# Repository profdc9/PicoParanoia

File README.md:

# PicoParanoia

This is an update to the ParanoiaBox ( https://www.github.com/profdc9/ParanoiaBox ) which uses a Raspberry Pi Pico rather than a STM32F103CBT6 Blue Pill.  It improves some security aspects of the original, such as having separate SPI ports for the ciphertext and plaintext cards.

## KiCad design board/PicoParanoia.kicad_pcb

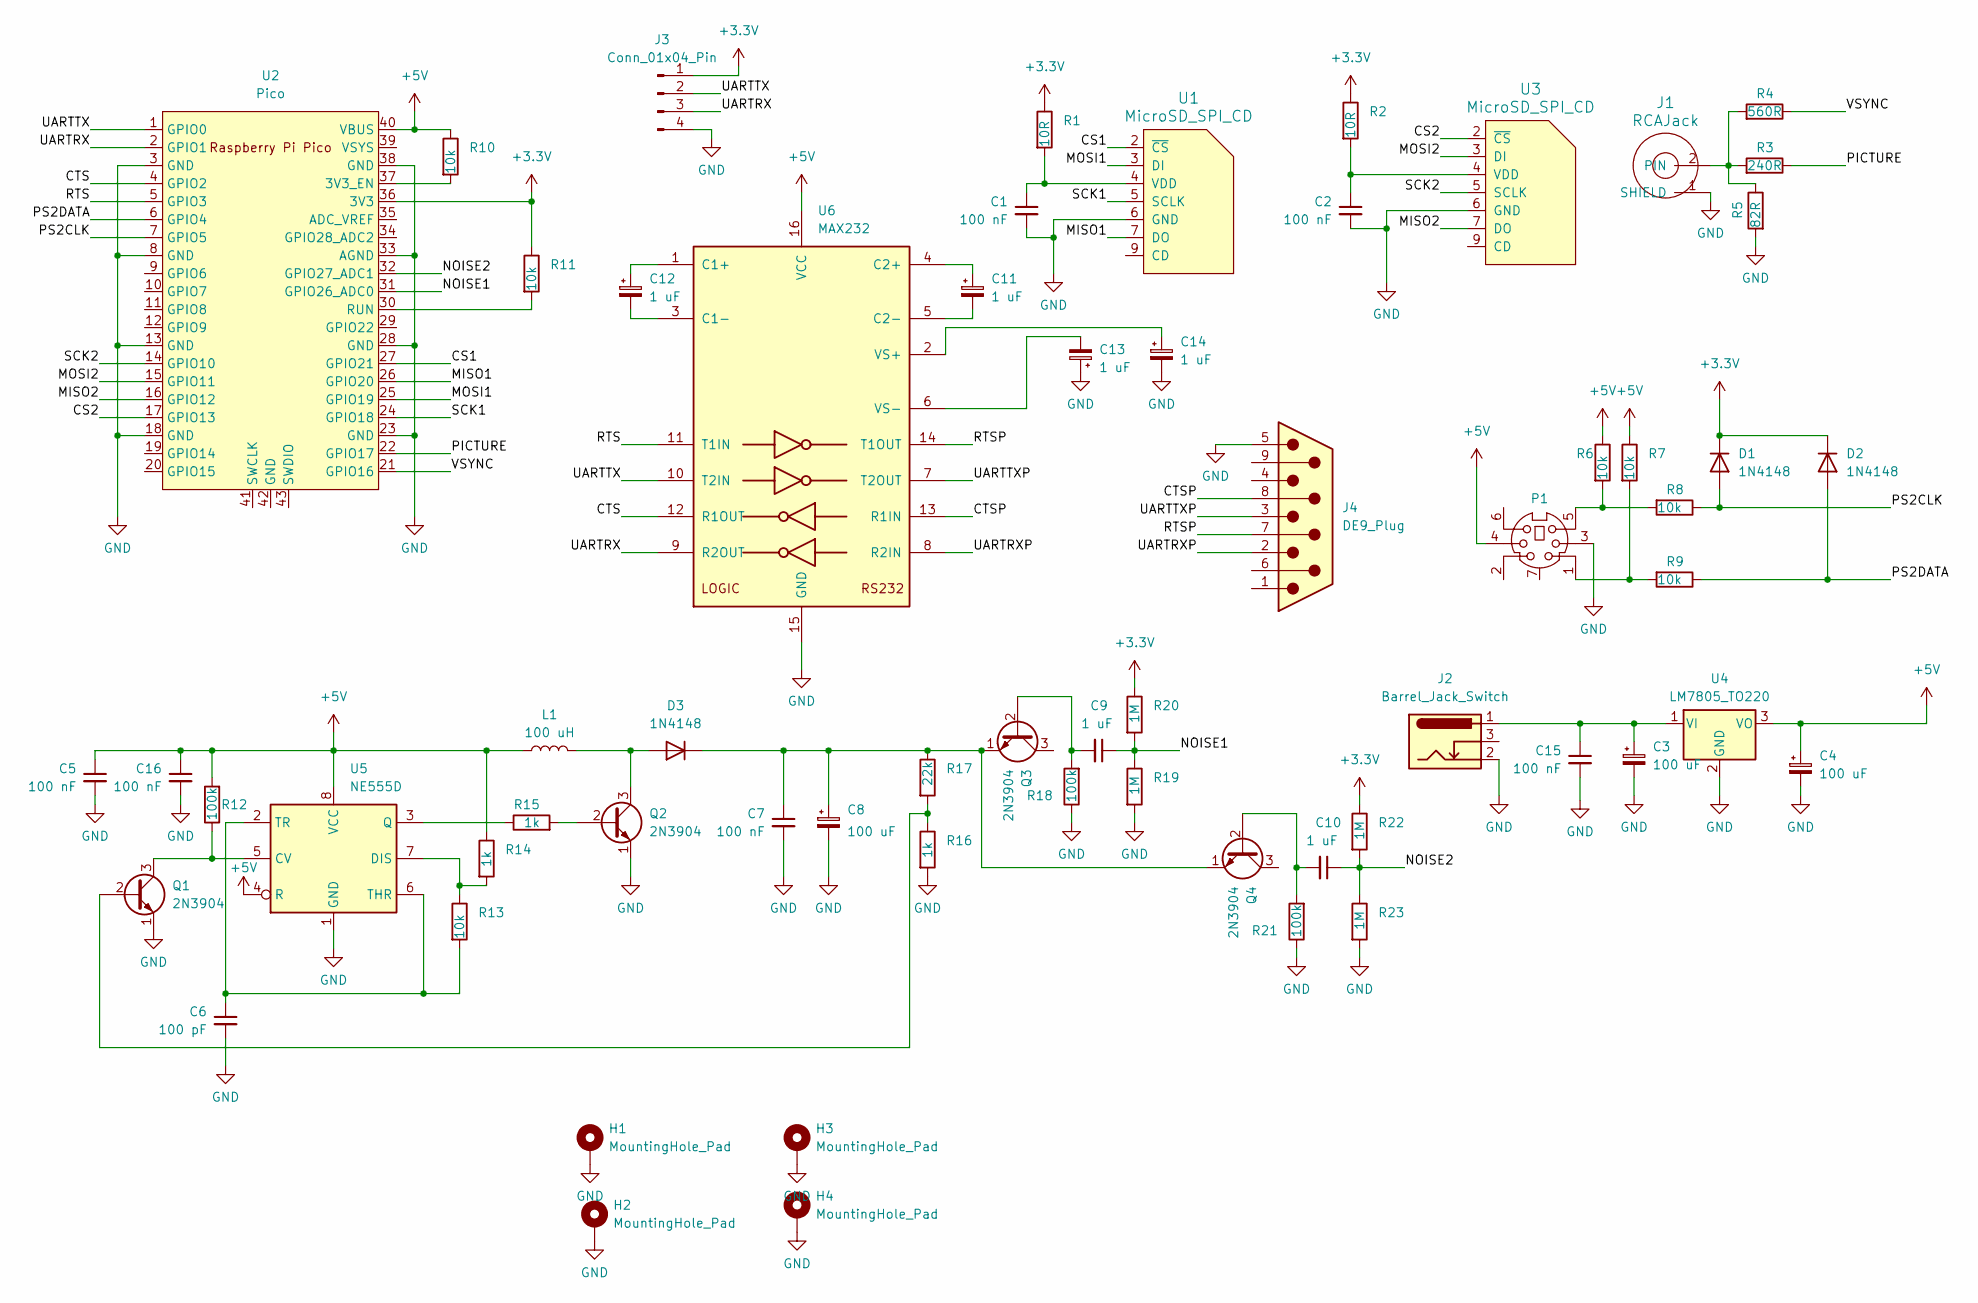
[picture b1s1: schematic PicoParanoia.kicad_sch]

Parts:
C1, C2, C5, C7, C15, C16: 100 nF; C_Disc_D5.0mm_W2.5mm_P5.00mm
C3, C4, C8: 100 uF; CP_Radial_D5.0mm_P2.50mm
C6: 100 pF; C_Disc_D5.0mm_W2.5mm_P5.00mm
C9, C10: 1 uF; C_Disc_D5.0mm_W2.5mm_P5.00mm
C11, C12, C13, C14: 1 uF; CP_Radial_D5.0mm_P2.50mm
D1, D2, D3: 1N4148; D_DO-41_SOD81_P7.62mm_Horizontal
H1, H2, H3, H4: MountingHole_Pad; MountingHole_3.2mm_M3_Pad
J1: RCAJack; RCAConnectorCommon
J2: Barrel_Jack_Switch; BarrelJack_Horizontal
J3: Conn_01x04_Pin; PinSocket_1x04_P2.54mm_Vertical
J4: DE9_Plug; DSUB-9_Male_Horizontal_P2.77x2.84mm_EdgePinOffset4.94mm_Hou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
L1: 100 uH; L_Axial_L7.0mm_D3.3mm_P12.70mm_Horizontal_Fastron_MICC
P1: Mini-DIN_6pins_ver4; Connector_Mini-DIN_Female_6Pin_2rows
Q1, Q2, Q3, Q4: 2N3904; TO-92_Inline_Wide
R1, R2: 10R; R_Axial_DIN0207_L6.3mm_D2.5mm_P7.62mm_Horizontal
R3: 240R; R_Axial_DIN0207_L6.3mm_D2.5mm_P7.62mm_Horizontal
R4: 560R; R_Axial_DIN0207_L6.3mm_D2.5mm_P7.62mm_Horizontal
R5: 82R; R_Axial_DIN0207_L6.3mm_D2.5mm_P7.62mm_Horizontal
R6, R7, R8, R9, R10, R11, R13: 10k; R_Axial_DIN0207_L6.3mm_D2.5mm_P7.62mm_Horizontal
R12, R18, R21: 100k; R_Axial_DIN0207_L6.3mm_D2.5mm_P7.62mm_Horizontal
R14, R15, R16: 1k; R_Axial_DIN0207_L6.3mm_D2.5mm_P7.62mm_Horizontal
R17: 22k; R_Axial_DIN0207_L6.3mm_D2.5mm_P7.62mm_Horizontal
R19, R20, R22, R23: 1M; R_Axial_DIN0207_L6.3mm_D2.5mm_P7.62mm_Horizontal
U1, U3: MicroSD_SPI_CD; GCT-MEM2055-00-190-01-A
U2: Pico; RPi_Pico_SMD_TH
U4: LM7805_TO220; TO-220-3_Vertical
U5: NE555D; DIP-8_W7.62mm_Socket
U6: MAX232; DIP-16_W7.62mm_Socket

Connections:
+3.3V: D1.1 (K), D2.1 (K), J3.1, R1.1, R2.1, R11.1, R20.1, R22.1, U2.36 (3V3)
+5V: C4.1, C5.1, C16.1, L1.1, P1.4, R6.1, R7.1, R10.1, R12.2, R14.1, U2.40 (VBUS), U4.3 (VO), U5.4 (R), U5.8 (VCC), U6.16 (VCC)
/CS1: U1.2 (~CS), U2.27 (GPIO21)
/CS2: U2.17 (GPIO13), U3.2 (~CS)
/CTS: U2.4 (GPIO2), U6.12 (R1OUT)
/CTSP: J4.8, U6.13 (R1IN)
/MISO1: U1.7 (DO), U2.26 (GPIO20)
/MISO2: U2.16 (GPIO12), U3.7 (DO)
/MOSI1: U1.3 (DI), U2.25 (GPIO19)
/MOSI2: U2.15 (GPIO11), U3.3 (DI)
/NOISE1: C9.1, R19.1, R20.2, U2.31 (GPIO26_ADC0)
/NOISE2: C10.1, R22.2, R23.1, U2.32 (GPIO27_ADC1)
/PICTURE: R3.1, U2.22 (GPIO17)
/PS2CLK: D1.2 (A), R8.1, U2.7 (GPIO5)
/PS2DATA: D2.2 (A), R9.1, U2.6 (GPIO4)
/RTS: U2.5 (GPIO3), U6.11 (T1IN)
/RTSP: J4.7, U6.14 (T1OUT)
/SCK1: U1.5 (SCLK), U2.24 (GPIO18)
/SCK2: U2.14 (GPIO10), U3.5 (SCLK)
/UARTRX: J3.3, U2.2 (GPIO1), U6.9 (R2OUT)
/UARTRXP: J4.2, U6.8 (R2IN)
/UARTTX: J3.2, U2.1 (GPIO0), U6.10 (T2IN)
/UARTTXP: J4.3, U6.7 (T2OUT)
/VSYNC: R4.1, U2.21 (GPIO16)
GND: C1.2, C2.2, C3.2, C4.2, C5.2, C6.2, C7.2, C8.2, C13.1, C14.2, C15.2, C16.2, H1.1, H2.1, H3.1, H4.1, J1.1 (SHIELD), J2.2, J3.4, J4.5, P1.3, Q1.1 (E), Q2.1 (E), R5.2, R16.2, R18.1, R19.2, R21.1, R23.2, U1.6 (GND), U2.3 (GND), U2.8 (GND), U2.13 (GND), U2.18 (GND), U2.23 (GND), U2.28 (GND), U2.33 (AGND), U2.38 (GND), U3.6 (GND), U4.2 (GND), U5.1 (GND), U6.15 (GND)
unnamed: D3.2 (A), L1.2, Q2.3 (C)
unnamed: C7.1, C8.1, D3.1 (K), Q3.1 (E), Q4.1 (E), R17.1
unnamed: J1.2 (PIN), R3.2, R4.2, R5.1
unnamed: P1.1, R7.2, R9.2
unnamed: P1.5, R6.2, R8.2
unnamed: Q1.2 (B), R16.1, R17.2
unnamed: Q1.3 (C), R12.1, U5.5 (CV)
unnamed: Q2.2 (B), R15.2
unnamed: C9.2, Q3.2 (B), R18.2
unnamed: C10.2, Q4.2 (B), R21.2
unnamed: C1.1, R1.2, U1.4 (VDD)
unnamed: R10.2, U2.37 (3V3_EN)
unnamed: R11.2, U2.30 (RUN)
unnamed: C2.1, R2.2, U3.4 (VDD)
unnamed: C3.1, C15.1, J2.1, U4.1 (VI)
unnamed: R13.1, R14.2, U5.7 (DIS)
unnamed: R15.1, U5.3 (Q)
unnamed: C6.1, R13.2, U5.2 (TR), U5.6 (THR)
unnamed: C12.1, U6.1 (C1+)
unnamed: C12.2, U6.3 (C1-)
unnamed: C11.1, U6.4 (C2+)
unnamed: C11.2, U6.5 (C2-)
unnamed: C14.1, U6.2 (VS+)
unnamed: C13.2, U6.6 (VS-)

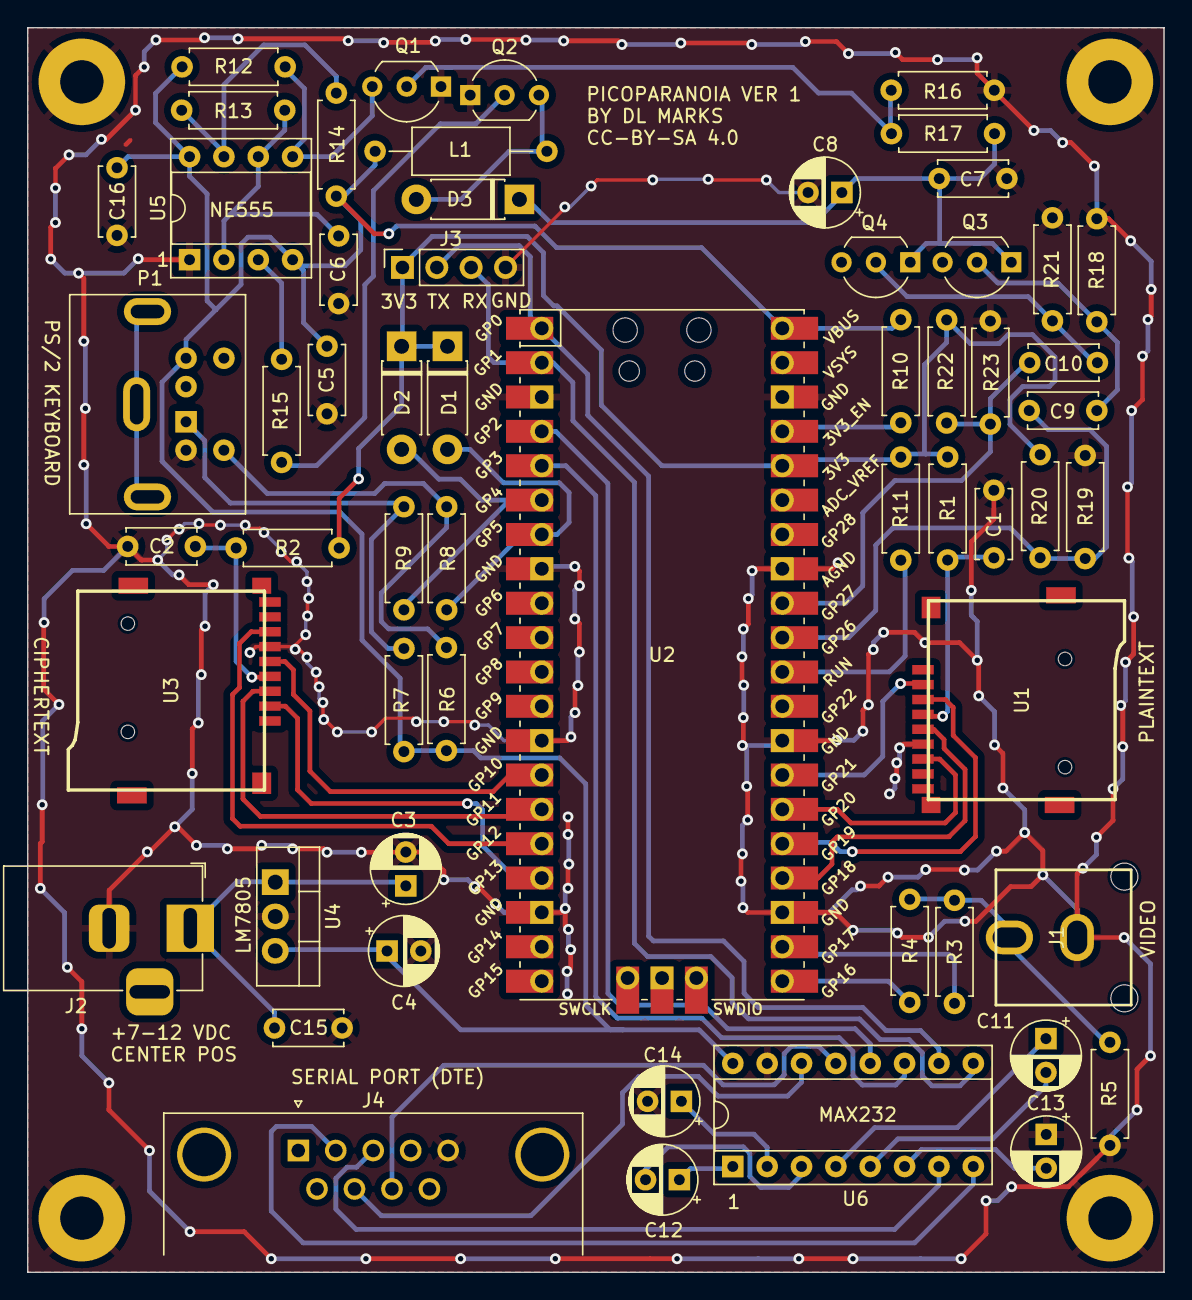
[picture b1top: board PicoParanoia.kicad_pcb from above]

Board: 2 copper layers, 84.0 x 92.0 mm, 62 parts (0 on the bottom side), 49 nets.

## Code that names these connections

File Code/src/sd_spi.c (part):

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// are on separate buses (PORTING.md §1.1/§2.3), so `curdrv` picks BOTH the SPI
// peripheral and its CS:
//
//   drive 0 = ciphertext -> hw spi1  (SCK GPIO10, MOSI GPIO11, MISO GPIO12, CS GPIO13)
//   drive 1 = plaintext  -> hw spi0  (SCK GPIO18, MOSI GPIO19, MISO GPIO20, CS GPIO21)

#include "ff.h"
#include "diskio.h"
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
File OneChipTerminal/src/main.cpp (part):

// OneChipTerminal — RP2040 port.
//
// PS/2 keyboard + NTSC TV VT100 terminal, bridged to a MAX232-level serial
// link on uart0 (GPIO0=TX, GPIO1=RX, GPIO2=CTS, GPIO3=RTS -- hardware flow
// control, PORTING notes in this repo's plan). Ported from the STM32/Bluepill
// OneChipTerminal.ino; the menu/config logic is largely unchanged, but two
// things differ from a literal port:
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//     still go through a write+notify path instead of a raw memcpy/memset.
//  2. RTS/CTS is real RP2040 UART hardware flow control (uart_set_hw_flow)
//     instead of the original's manually bit-banged GPIOs + software FIFO
//     high-watermark logic -- this board's GPIO2/3 are already the uart0
//     hardware CTS/RTS pins. One behavioral consequence: toggling
//     ser_state.rtscts must now actively reprogram the UART peripheral
//     (do_flow_control() below), where the original could get away with just
//     flipping a flag consulted by the software bit-bang in loop().
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
  gpio_set_function(0, GPIO_FUNC_UART);   // TX
  gpio_set_function(1, GPIO_FUNC_UART);   // RX
  gpio_set_function(2, GPIO_FUNC_UART);   // CTS
  gpio_set_function(3, GPIO_FUNC_UART);   // RTS
  uart_init(uart0, 19200);
  setup_serial_port(&ser_state);

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
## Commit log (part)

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2025-09-06 JLCPCB order
2025-09-16 Swapped cipher and plaintext cards

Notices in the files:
OneChipTerminal/src/main.cpp:
"zLib license for software, CC-BY-SA 4.0 for hardware\r
board/PicoParanoia.kicad_pcb:
CC-BY-SA 4.0
